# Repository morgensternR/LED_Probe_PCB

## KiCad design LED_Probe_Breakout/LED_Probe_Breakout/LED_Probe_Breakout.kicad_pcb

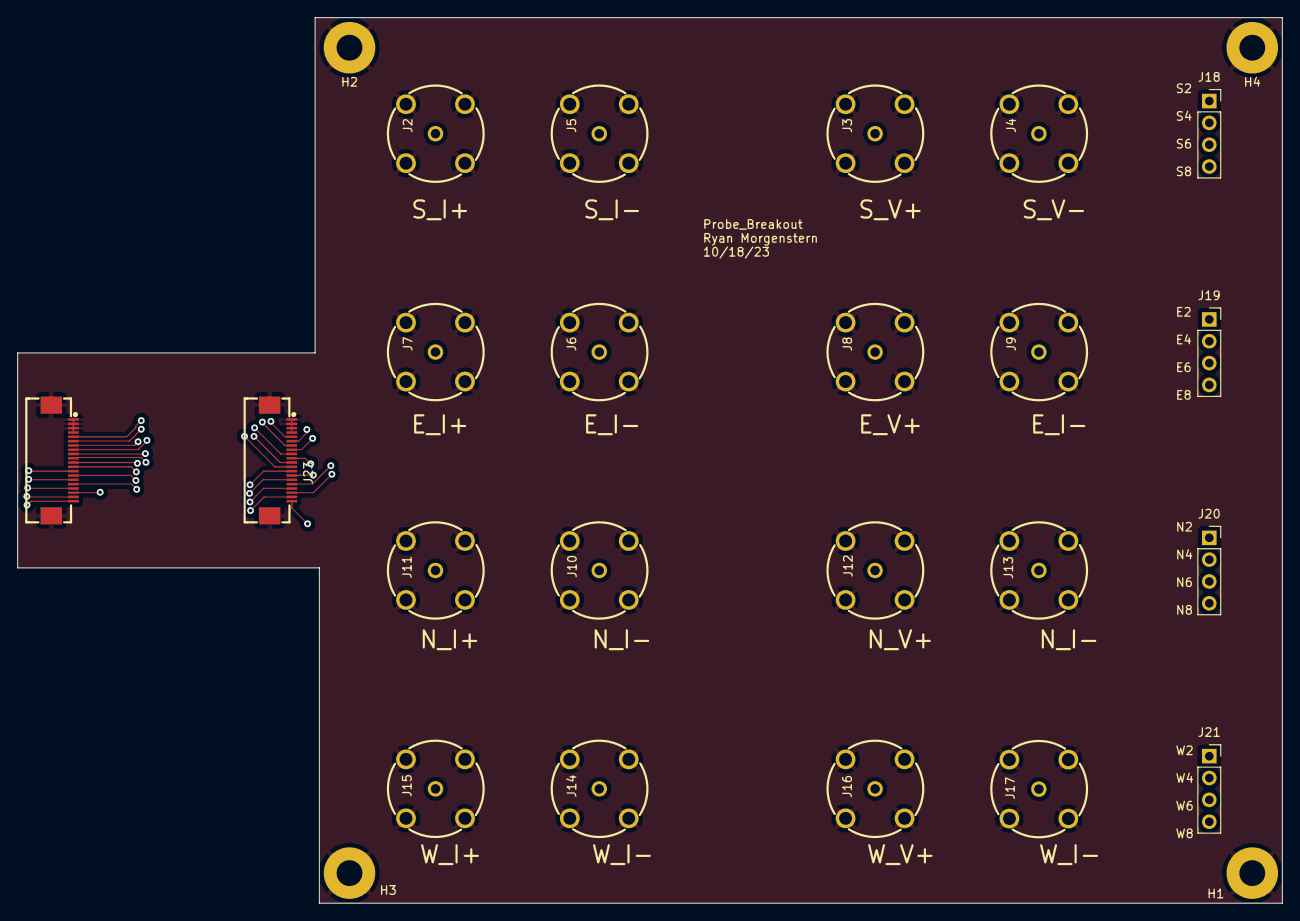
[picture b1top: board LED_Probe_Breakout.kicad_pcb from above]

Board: 4 copper layers, 147.1 x 103.0 mm, 26 parts (0 on the bottom side), 33 nets.

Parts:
H1, H2, H3, H4: MountingHole_Pad; MountingHole_3mm_Pad
J2, J3, J4, J5, J6, J7, J8, J9, J10, J11, J12, J13, J14, J15, J16, J17: Conn_Coaxial; ANT-TH_DOSIN-801-0057
J18, J19, J20, J21: Conn_01x04_Socket; PinSocket_1x04_P2.54mm_Vertical
J22, J23: Conn_01x22; FPC-SMD_20P-P0.50_XUNPU_FPC-05F-20PH20

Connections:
/E_I+: J7.1 (In), J22.12
/E_I-: J6.1 (In), J22.6
/E_V+: J8.1 (In), J22.10
/E_V-: J9.1 (In), J22.8
/N_I+: J11.1 (In), J23.20
/N_I-: J10.1 (In), J23.14
/N_V+: J12.1 (In), J23.18
/N_V-: J13.1 (In), J23.16
/S_I+: J2.1 (In), J22.20
/S_I-: J5.1 (In), J22.14
/S_V+: J3.1 (In), J22.18
/S_V-: J4.1 (In), J22.16
/Solder_Point_Breakout1/Sig_1: J19.1, J22.11
/Solder_Point_Breakout1/Sig_2: J19.2, J22.9
/Solder_Point_Breakout1/Sig_3: J19.3, J22.7
/Solder_Point_Breakout1/Sig_4: J19.4, J22.5
/Solder_Point_Breakout2/Sig_1: J20.1, J23.19
/Solder_Point_Breakout2/Sig_2: J20.2, J23.17
/Solder_Point_Breakout2/Sig_3: J20.3, J23.15
/Solder_Point_Breakout2/Sig_4: J20.4, J23.13
/Solder_Point_Breakout3/Sig_1: J21.1, J23.11
/Solder_Point_Breakout3/Sig_2: J21.2, J23.9
/Solder_Point_Breakout3/Sig_3: J21.3, J23.7
/Solder_Point_Breakout3/Sig_4: J21.4, J23.5
/Solder_Point_Breakout/Sig_1: J18.1, J22.19
/Solder_Point_Breakout/Sig_2: J18.2, J22.17
/Solder_Point_Breakout/Sig_3: J18.3, J22.15
/Solder_Point_Breakout/Sig_4: J18.4, J22.13
/W_I+: J15.1 (In), J23.12
/W_I-: J14.1 (In), J23.6
/W_V+: J16.1 (In), J23.10
/W_V-: J17.1 (In), J23.8
GND: H1.1, H2.1, H3.1, H4.1, J2.2 (Ext), J3.2 (Ext), J4.2 (Ext), J5.2 (Ext), J6.2 (Ext), J7.2 (Ext), J8.2 (Ext), J9.2 (Ext), J10.2 (Ext), J11.2 (Ext), J12.2 (Ext), J13.2 (Ext), J14.2 (Ext), J15.2 (Ext), J16.2 (Ext), J17.2 (Ext), J22.1, J22.2, J22.3, J22.4, J22.21, J22.22, J23.1, J23.2, J23.3, J23.4, J23.21, J23.22

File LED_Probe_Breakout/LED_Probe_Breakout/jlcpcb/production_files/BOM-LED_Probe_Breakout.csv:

Comment,Designator,Footprint,LCSC
Conn_01x22,"J22,J23",FPC-SMD_20P-P0.50_XUNPU_FPC-05F-20PH20,C2856803
Conn_Coaxial,J14,ANT-TH_DOSIN-801-0057,
Conn_Coaxial,J4,ANT-TH_DOSIN-801-0057,
Conn_Coaxial,J17,ANT-TH_DOSIN-801-0057,
Conn_Coaxial,J10,ANT-TH_DOSIN-801-0057,
Conn_Coaxial,J6,ANT-TH_DOSIN-801-0057,
MountingHole_Pad,H4,MountingHole_3mm_Pad,
Conn_01x04_Socket,J21,PinSocket_1x04_P2.54mm_Vertical,
Conn_Coaxial,J3,ANT-TH_DOSIN-801-0057,
Conn_Coaxial,J11,ANT-TH_DOSIN-801-0057,
Conn_01x04_Socket,J19,PinSocket_1x04_P2.54mm_Vertical,
Conn_01x04_Socket,J20,PinSocket_1x04_P2.54mm_Vertical,
Conn_Coaxial,J7,ANT-TH_DOSIN-801-0057,
MountingHole_Pad,H1,MountingHole_3mm_Pad,
Conn_01x04_Socket,J18,PinSocket_1x04_P2.54mm_Vertical,
Conn_Coaxial,J15,ANT-TH_DOSIN-801-0057,
Conn_Coaxial,J5,ANT-TH_DOSIN-801-0057,
Conn_Coaxial,J2,ANT-TH_DOSIN-801-0057,
MountingHole_Pad,H3,MountingHole_3mm_Pad,
Conn_Coaxial,J12,ANT-TH_DOSIN-801-0057,
Conn_Coaxial,J8,ANT-TH_DOSIN-801-0057,
Conn_Coaxial,J9,ANT-TH_DOSIN-801-0057,
Conn_Coaxial,J13,ANT-TH_DOSIN-801-0057,
Conn_Coaxial,J16,ANT-TH_DOSIN-801-0057,
MountingHole_Pad,H2,MountingHole_3mm_Pad,

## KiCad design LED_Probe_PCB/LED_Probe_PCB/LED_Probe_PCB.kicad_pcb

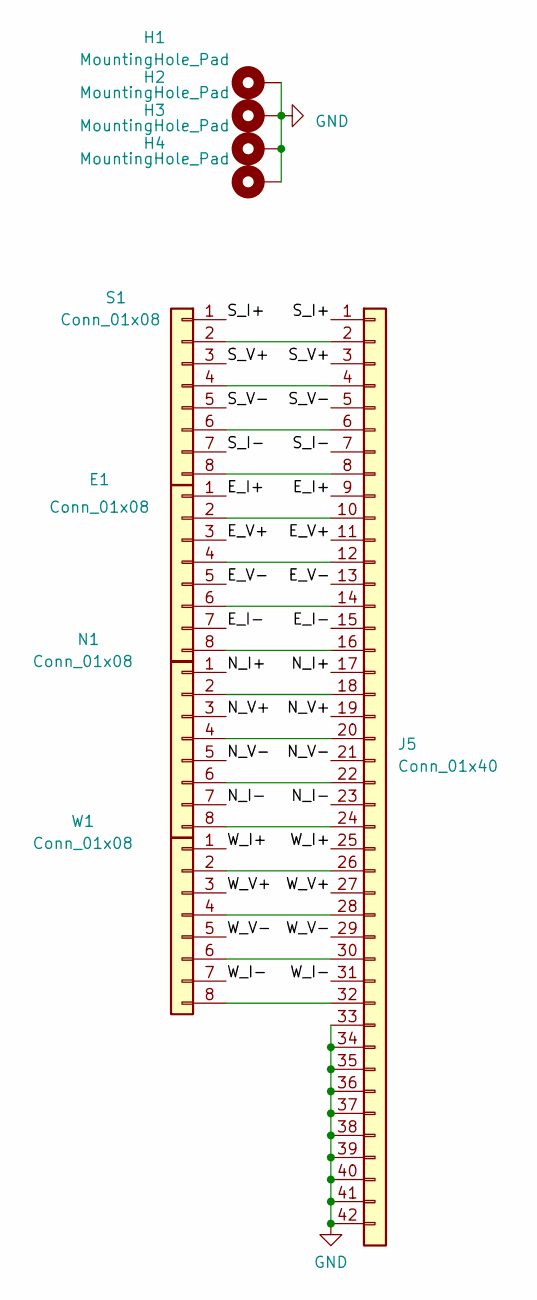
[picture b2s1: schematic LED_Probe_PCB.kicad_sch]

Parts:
E1: Conn_01x08; wirebond_8x_0.6x2cm
H1, H2, H3, H4: MountingHole_Pad; MountingHole_2.2mm_M2_DIN965_Pad
J5: Conn_01x40; FPC-SMD_P0.50-40P_FGS-XJ-H2.0; LCSC C262674
N1: Conn_01x08; wirebond_8x_0.6x2cm
S1: Conn_01x08; wirebond_8x_0.6x2cm
W1: Conn_01x08; wirebond_8x_0.6x2cm

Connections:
/E_I+: E1.1, J5.9
/E_I-: E1.7, J5.15
/E_V+: E1.3, J5.11
/E_V-: E1.5, J5.13
/N_I+: J5.17, N1.1
/N_I-: J5.23, N1.7
/N_V+: J5.19, N1.3
/N_V-: J5.21, N1.5
/S_I+: J5.1, S1.1
/S_I-: J5.7, S1.7
/S_V+: J5.3, S1.3
/S_V-: J5.5, S1.5
/W_I+: J5.25, W1.1
/W_I-: J5.31, W1.7
/W_V+: J5.27, W1.3
/W_V-: J5.29, W1.5
GND: H1.1, H2.1, H3.1, H4.1, J5.33, J5.34, J5.35, J5.36, J5.37, J5.38, J5.39, J5.40, J5.41, J5.42
unnamed: E1.2, J5.10
unnamed: E1.4, J5.12
unnamed: E1.6, J5.14
unnamed: E1.8, J5.16
unnamed: J5.2, S1.2
unnamed: J5.4, S1.4
unnamed: J5.6, S1.6
unnamed: J5.8, S1.8
unnamed: J5.18, N1.2
unnamed: J5.20, N1.4
unnamed: J5.22, N1.6
unnamed: J5.24, N1.8
unnamed: J5.26, W1.2
unnamed: J5.28, W1.4
unnamed: J5.30, W1.6
unnamed: J5.32, W1.8

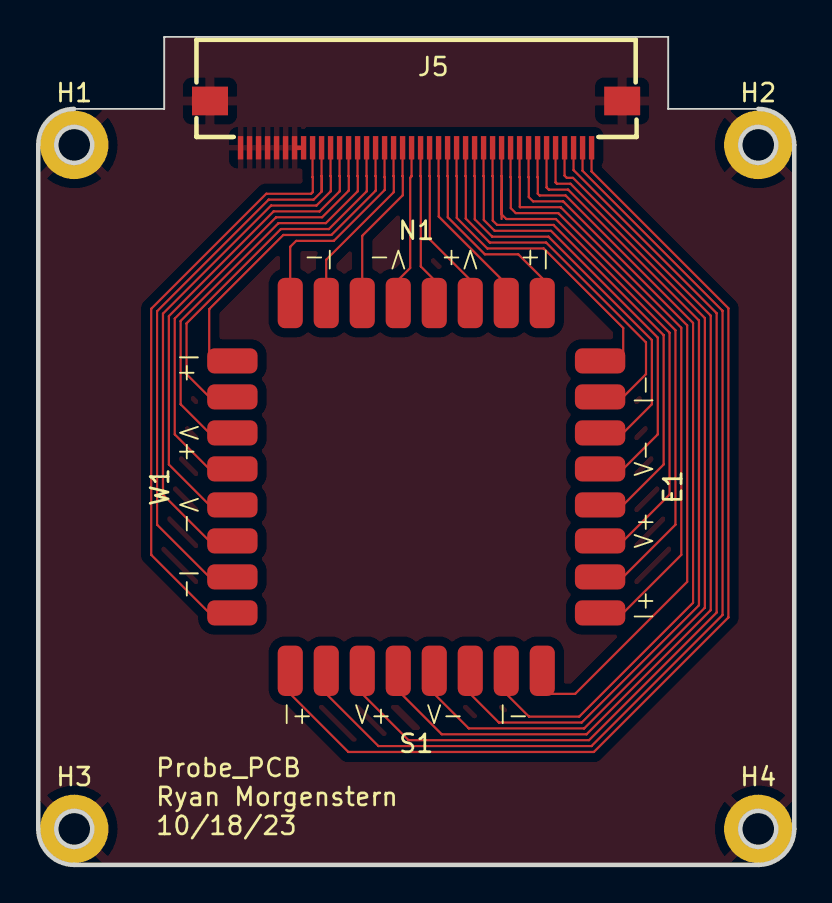
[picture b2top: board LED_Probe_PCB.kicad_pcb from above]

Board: 2 copper layers, 42.0 x 45.9 mm, 9 parts (0 on the bottom side), 33 nets.

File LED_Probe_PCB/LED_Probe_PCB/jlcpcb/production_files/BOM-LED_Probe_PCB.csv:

Comment,Designator,Footprint,LCSC
Conn_01x40,J5,FPC-SMD_P0.50-40P_FGS-XJ-H2.0,C262674
MountingHole_Pad,H2,MountingHole_2.2mm_M2_DIN965_Pad,
Conn_01x08,S1,wirebond_8x_0.6x2cm,
Conn_01x08,E1,wirebond_8x_0.6x2cm,
Conn_01x08,W1,wirebond_8x_0.6x2cm,
Conn_01x08,N1,wirebond_8x_0.6x2cm,
MountingHole_Pad,H4,MountingHole_2.2mm_M2_DIN965_Pad,
MountingHole_Pad,H3,MountingHole_2.2mm_M2_DIN965_Pad,
MountingHole_Pad,H1,MountingHole_2.2mm_M2_DIN965_Pad,

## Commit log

2023-10-20 updated production files
2023-10-27 update to 2x 20P
2023-12-04 Breakout Board update
    flipped connector pinout
    made connectors inline
